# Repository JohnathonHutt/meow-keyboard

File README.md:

# Meow Keyboard

An 18-key unibody keyboard

This keyboard was inspired by Ben Vallack and his 18 key unibody board (which this is basically just a clone of).

Big thanks to kilipan (https://github.com/kilipan) who was kind enough to design this PCB for me, I just added the artwork.

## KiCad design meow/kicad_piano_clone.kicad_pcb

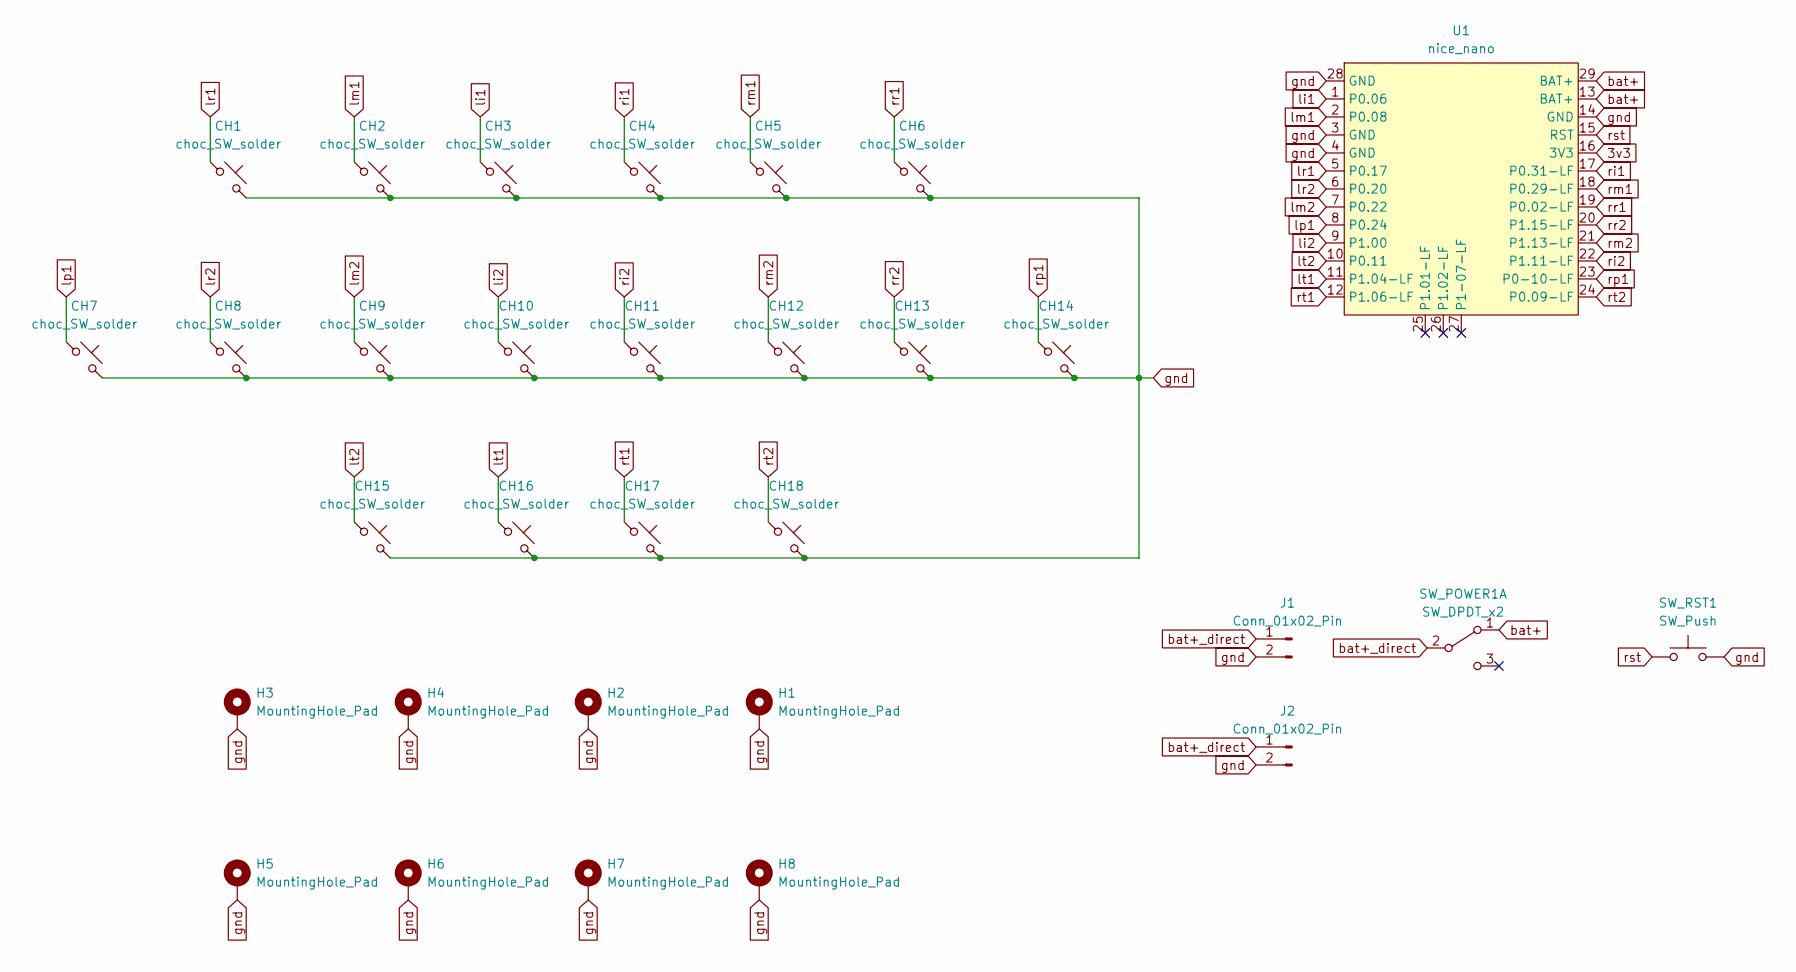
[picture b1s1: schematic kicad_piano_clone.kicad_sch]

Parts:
CH1, CH2, CH3, CH4, CH5, CH6, CH8, CH9, CH10, CH11, CH12, CH13: choc_SW_solder; SW_choc_v1_HS_CPG135001S30_1u
CH7, CH14, CH15, CH16, CH17, CH18: choc_SW_solder; SW_choc_v1_HS_CPG135001S30_1.5u
H1, H2, H3, H4, H5, H6, H7, H8: MountingHole_Pad; MountingHole_2.2mm_M2_Pad_Via_nosilk
J1: Conn_01x02_Pin; JST_GH_SM02B-GHS-TB_1x02-1MP_P1.25mm_Horizontal
J2: Conn_01x02_Pin; PinHeader_1x02_P2.54mm_Vertical
SW_POWER1: SW_DPDT_x2; SW_MSK12C02-HB
SW_RST1: SW_Push; SW_ResetSW
U1: nice_nano; nice_nano_AH_USBup

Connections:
3v3: U1.16 (3V3)
bat+: SW_POWER1.1 (A), U1.13 (BAT+), U1.29 (BAT+)
bat+_direct: J1.1, J2.1, SW_POWER1.2 (B)
gnd: CH1.2, CH2.2, CH3.2, CH4.2, CH5.2, CH6.2, CH7.2, CH8.2, CH9.2, CH10.2, CH11.2, CH12.2, CH13.2, CH14.2, CH15.2, CH16.2, CH17.2, CH18.2, H1.1, H2.1, H3.1, H4.1, H5.1, H6.1, H7.1, H8.1, J1.2, J2.2, SW_RST1.2, U1.3 (GND), U1.4 (GND), U1.14 (GND), U1.28 (GND)
li1: CH3.1, U1.1 (P0.06)
li2: CH10.1, U1.9 (P1.00)
lm1: CH2.1, U1.2 (P0.08)
lm2: CH9.1, U1.7 (P0.22)
lp1: CH7.1, U1.8 (P0.24)
lr1: CH1.1, U1.5 (P0.17)
lr2: CH8.1, U1.6 (P0.20)
lt1: CH16.1, U1.11 (P1.04-LF)
lt2: CH15.1, U1.10 (P0.11)
ri1: CH4.1, U1.17 (P0.31-LF)
ri2: CH11.1, U1.22 (P1.11-LF)
rm1: CH5.1, U1.18 (P0.29-LF)
rm2: CH12.1, U1.21 (P1.13-LF)
rp1: CH14.1, U1.23 (P0-10-LF)
rr1: CH6.1, U1.19 (P0.02-LF)
rr2: CH13.1, U1.20 (P1.15-LF)
rst: SW_RST1.1, U1.15 (RST)
rt1: CH17.1, U1.12 (P1.06-LF)
rt2: CH18.1, U1.24 (P0.09-LF)

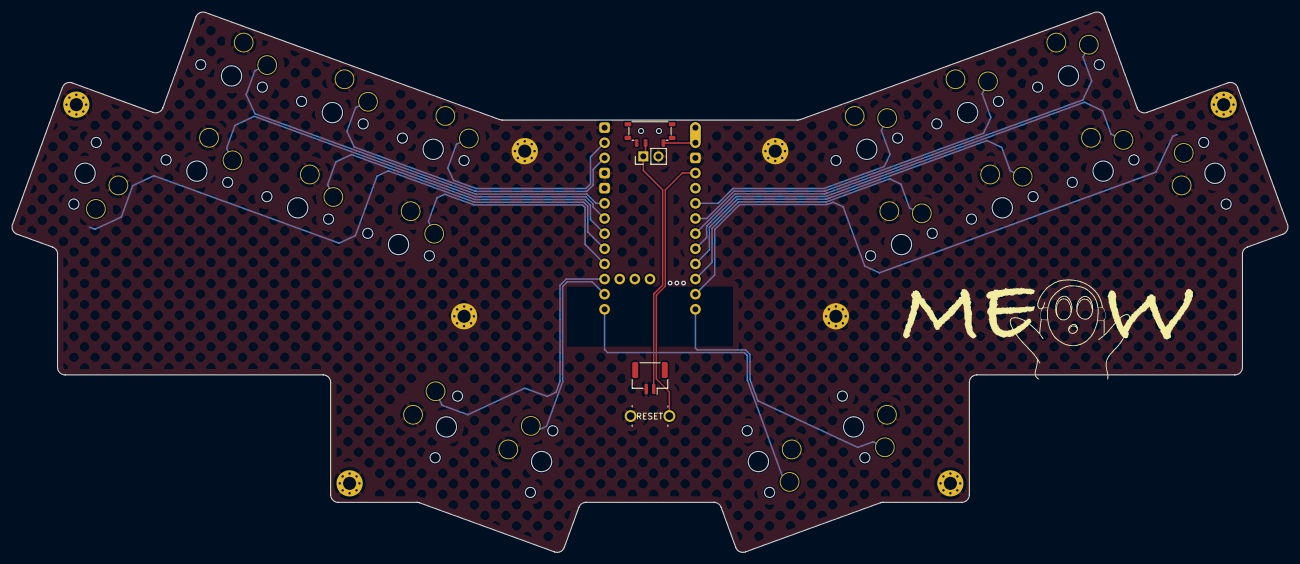
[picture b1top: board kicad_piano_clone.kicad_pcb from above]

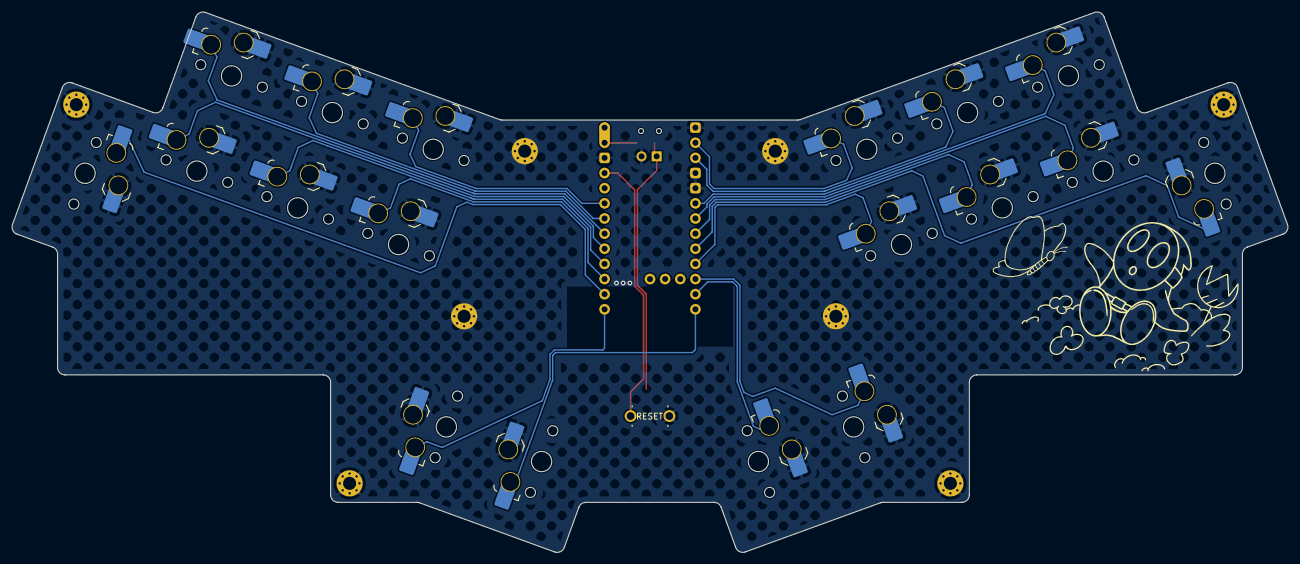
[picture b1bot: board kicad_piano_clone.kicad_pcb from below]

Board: 2 copper layers, 214.0 x 90.6 mm, 33 parts (19 on the bottom side), 22 nets.

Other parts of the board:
fluttershy: LOGO
meow: LOGO

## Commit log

2024-08-23 Create images directory
2024-08-23 Add images folder, readme, and gitignore
